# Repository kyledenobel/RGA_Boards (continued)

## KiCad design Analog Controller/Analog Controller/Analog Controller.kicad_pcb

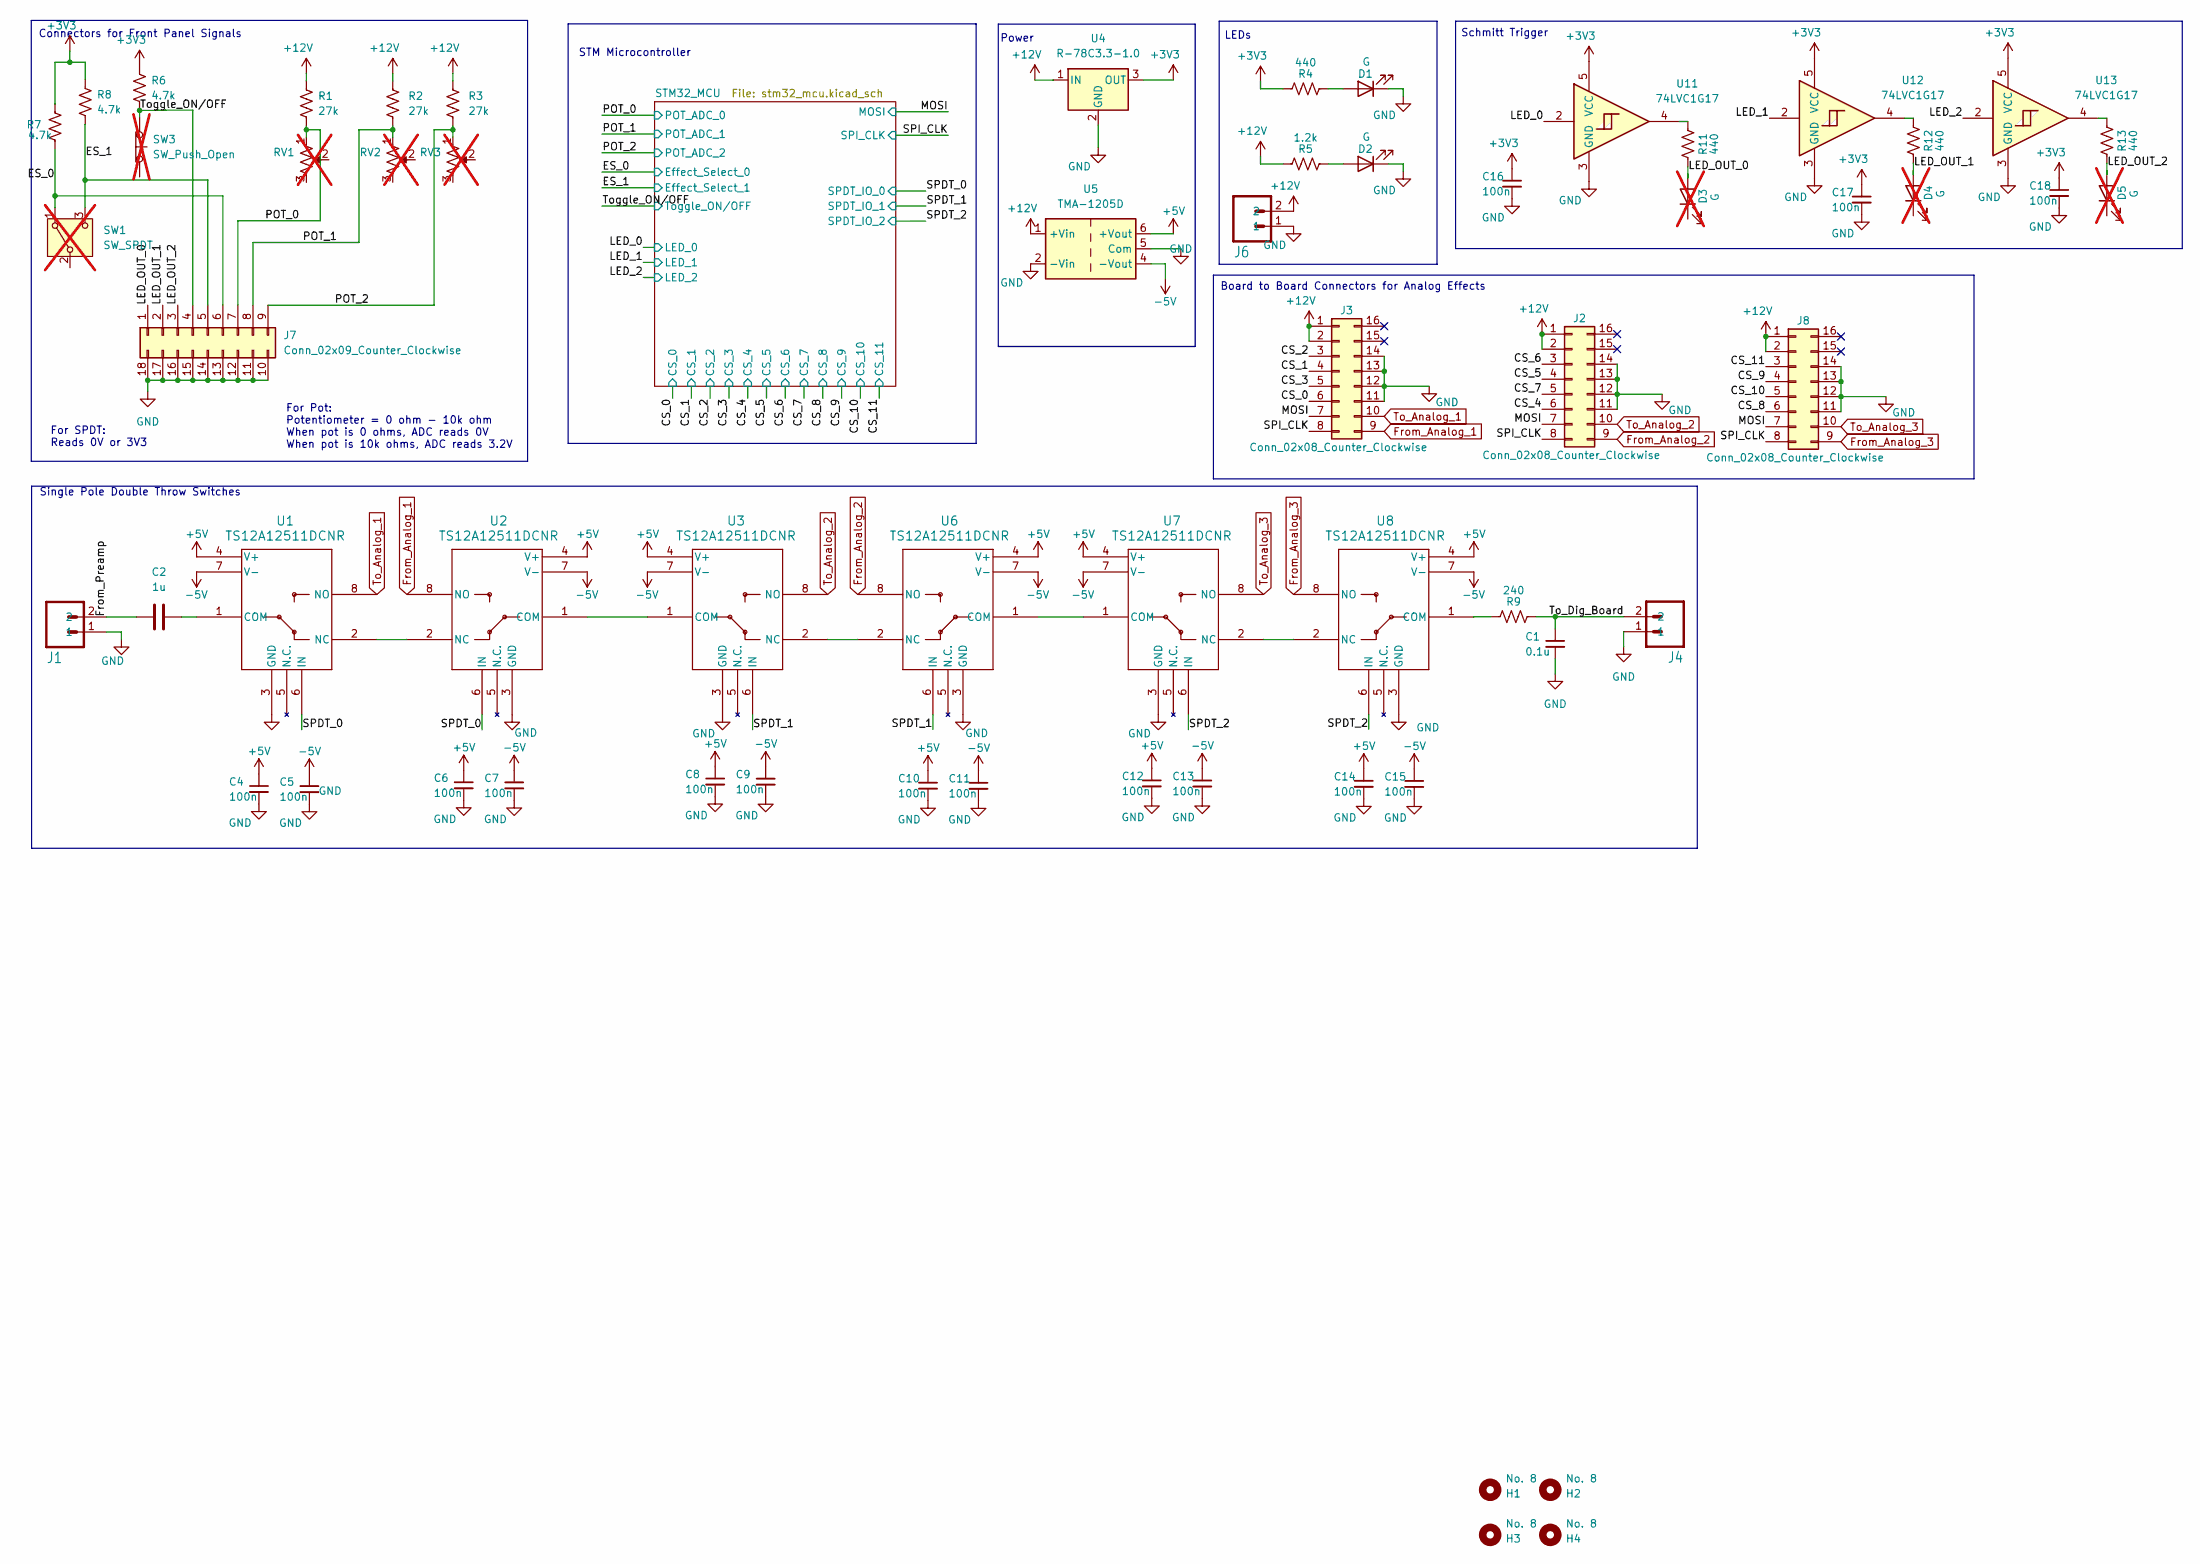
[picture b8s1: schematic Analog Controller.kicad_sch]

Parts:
C1: 0.1u; R_0603_1608Metric_Pad0.98x0.95mm_HandSolder
C2: 1u; C_0603_1608Metric
C4, C5, C6, C7, C8, C9, C10, C11, C12, C13, C14, C15, C16, C17, C18: 100n; R_0603_1608Metric_Pad0.98x0.95mm_HandSolder
D1, D2: G; LED_0603_1608Metric_Pad1.05x0.95mm_HandSolder
D3, D4, D5: G; LED_0603_1608Metric_Pad1.05x0.95mm_HandSolder; not fitted
H1, H2, H3, H4: No. 8; MountingHole_3.2mm_M3
J1, J4: MINIFIT-2-VERT; Molex_Mini-Fit_Jr_5566-02A_2x01_P4.20mm_Vertical
J2, J3, J8: Conn_02x08_Counter_Clockwise; PinSocket_2x08_P2.54mm_Vertical
J6: MINIFIT-2-VERT; Molex_Mega-Fit_76829-0102_2x01_P5.70mm_Vertical
J7: Conn_02x09_Counter_Clockwise; Molex_Micro-Fit_3.0_43045-1812_2x09_P3.00mm_Vertical
R1, R2, R3: 27k; R_0603_1608Metric_Pad0.98x0.95mm_HandSolder
R4, R11, R12, R13: 440; R_0603_1608Metric_Pad0.98x0.95mm_HandSolder
R5: 1.2k; R_0603_1608Metric_Pad0.98x0.95mm_HandSolder
R6, R7, R8: 4.7k; R_0603_1608Metric_Pad0.98x0.95mm_HandSolder
R9: 240; R_0603_1608Metric_Pad0.98x0.95mm_HandSolder
RV1, RV2, RV3: R_Potentiometer_US; not fitted
SW1: SW_SPDT; not fitted
SW3: SW_Push_Open; not fitted
U1, U2, U3, U6, U7, U8: TS12A12511DCNR; DCN8
U4: R-78C3.3-1.0; Converter_DCDC_RECOM_R-78E-0.5_THT
U5: TMA-1205D; Converter_DCDC_TRACO_TMA-05xxD_12xxD_Dual_THT
U11, U12, U13: 74LVC1G17; SOT-23-5

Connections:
+3V3: C16.1, C17.1, C18.1, R4.2, R6.1, R7.1, R8.1, U4.3 (OUT), U11.5 (VCC), U12.5 (VCC), U13.5 (VCC); also elsewhere on the board
+5V: C4.1, C6.1, C8.1, C10.1, C12.1, C14.1, U1.4 (V+), U2.4 (V+), U3.4 (V+), U5.6 (+Vout), U6.4 (V+), U7.4 (V+), U8.4 (V+)
+12V: J2.1, J2.2, J3.1, J3.2, J6.2, J8.1, J8.2, R1.1, R2.1, R3.1, R5.2, U4.1 (IN), U5.1 (+Vin)
-5V: C5.1, C7.1, C9.1, C11.1, C13.1, C15.1, U1.7 (V-), U2.7 (V-), U3.7 (V-), U5.4 (-Vout), U6.7 (V-), U7.7 (V-), U8.7 (V-)
/CS_0: J3.6; also elsewhere on the board
/CS_1: J3.4; also elsewhere on the board
/CS_2: J3.3; also elsewhere on the board
/CS_3: J3.5; also elsewhere on the board
/CS_4: J2.6; also elsewhere on the board
/CS_5: J2.4; also elsewhere on the board
/CS_6: J2.3; also elsewhere on the board
/CS_7: J2.5; also elsewhere on the board
/CS_8: J8.6; also elsewhere on the board
/CS_9: J8.4; also elsewhere on the board
/CS_10: J8.5; also elsewhere on the board
/CS_11: J8.3; also elsewhere on the board
/ES_0: J7.6, R7.2, SW1.1 (A); also elsewhere on the board
/ES_1: J7.5, R8.2, SW1.3 (C); also elsewhere on the board
/From_Preamp: C2.1, J1.2
/LED_0: U11.2; also elsewhere on the board
/LED_1: U12.2; also elsewhere on the board
/LED_2: U13.2; also elsewhere on the board
/LED_OUT_0: D3.2 (A), J7.1, R11.1
/LED_OUT_1: D4.2 (A), J7.2, R12.1
/LED_OUT_2: D5.2 (A), J7.3, R13.1
/MOSI: J2.7, J3.7, J8.7; also elsewhere on the board
/POT_0: J7.7, R1.2, RV1.1; also elsewhere on the board
/POT_1: J7.8, R2.2, RV2.1; also elsewhere on the board
/POT_2: J7.9, R3.2, RV3.1; also elsewhere on the board
/SPDT_0: U1.6 (IN), U2.6 (IN); also elsewhere on the board
/SPDT_1: U3.6 (IN), U6.6 (IN); also elsewhere on the board
/SPDT_2: U7.6 (IN), U8.6 (IN); also elsewhere on the board
/SPI_CLK: J2.8, J3.8, J8.8; also elsewhere on the board
/To_Dig_Board: C1.1, J4.2, R9.1
/Toggle_ON/OFF: J7.4, R6.2, SW3.1 (A); also elsewhere on the board
From_Analog_1: J3.9, U2.8 (NO)
From_Analog_2: J2.9, U6.8 (NO)
From_Analog_3: J8.9, U8.8 (NO)
GND: C1.2, C4.2, C5.2, C6.2, C7.2, C8.2, C9.2, C10.2, C11.2, C12.2, C13.2, C14.2, C15.2, C16.2, C17.2, C18.2, D1.1 (K), D2.1 (K), J1.1, J2.11, J2.12, J2.13, J2.14, J3.11, J3.12, J3.13, J3.14, J4.1, J6.1, J7.10, J7.11, J7.12, J7.13, J7.14, J7.15, J7.16, J7.17, J7.18, J8.11, J8.12, J8.13, J8.14, U1.3 (GND), U2.3 (GND), U3.3 (GND), U4.2 (GND), U5.2 (-Vin), U5.5 (Com), U6.3 (GND), U7.3 (GND), U8.3 (GND), U11.3 (GND), U12.3 (GND), U13.3 (GND); also elsewhere on the board
unnamed: D1.2 (A), R4.1
unnamed: D2.2 (A), R5.1
unnamed: R11.2, U11.4
unnamed: R12.2, U12.4
unnamed: R13.2, U13.4
unnamed: C2.2, U1.1 (COM)
unnamed: U1.2 (NC), U2.2 (NC)
unnamed: U2.1 (COM), U3.1 (COM)
unnamed: U3.2 (NC), U6.2 (NC)
unnamed: U6.1 (COM), U7.1 (COM)
unnamed: U7.2 (NC), U8.2 (NC)
unnamed: R9.2, U8.1 (COM)
To_Analog_1: J3.10, U1.8 (NO)
To_Analog_2: J2.10, U3.8 (NO)
To_Analog_3: J8.10, U7.8 (NO)

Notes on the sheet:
LEDs
For SPDT: Reads 0V or 3V3
Connectors for Front Panel Signals
Schmitt Trigger
STM Microcontroller
For Pot: Potentiometer = 0 ohm - 10k ohm When pot is 0 ohms, ADC reads 0V When pot is 10k ohms, ADC reads 3.2V
Board to Board Connectors for Analog Effects
Power
Single Pole Double Throw Switches

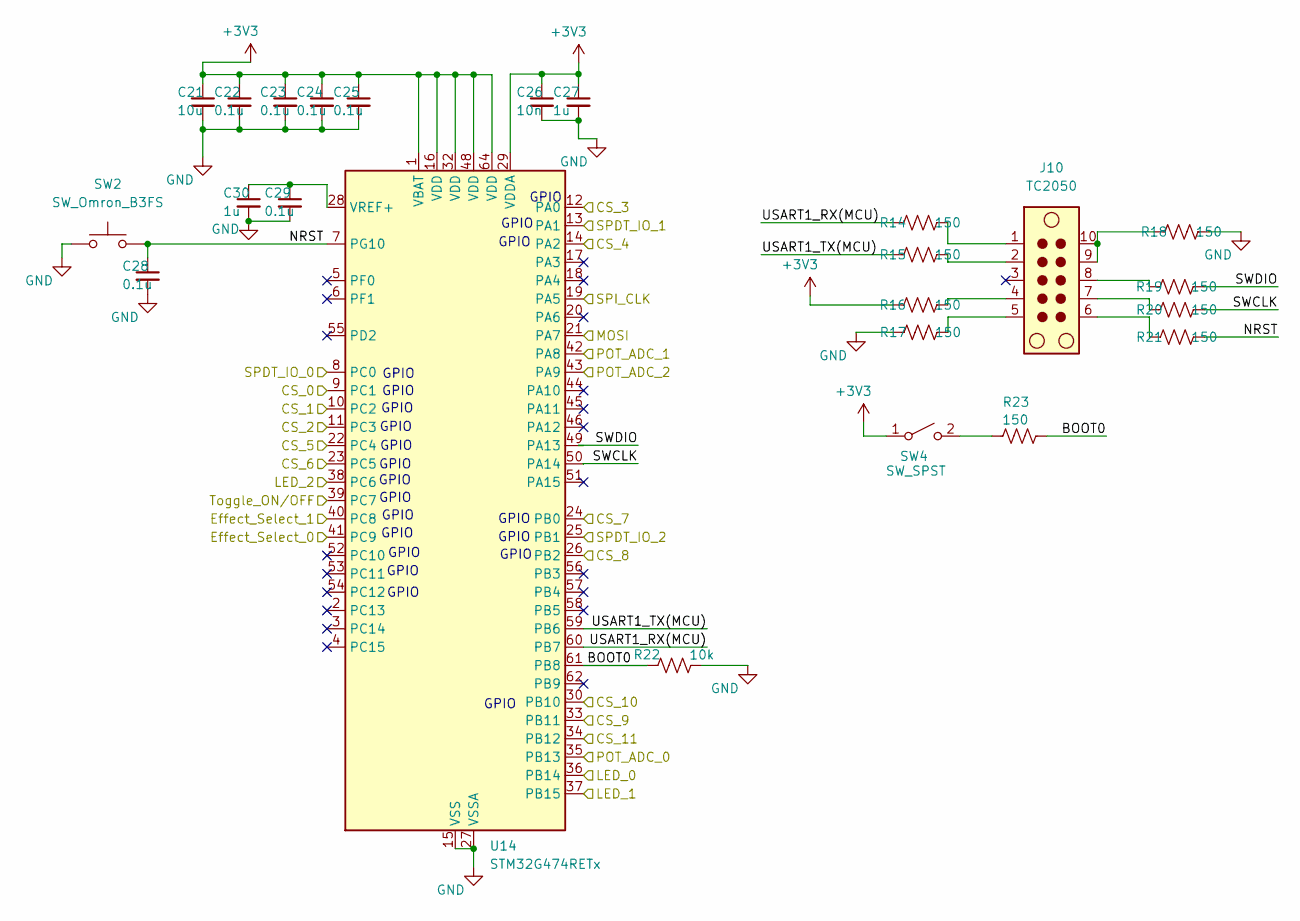
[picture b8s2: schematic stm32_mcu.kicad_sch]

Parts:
C21: 10u; R_0603_1608Metric_Pad0.98x0.95mm_HandSolder
C22, C23, C24, C25, C28, C29: 0.1u; R_0603_1608Metric_Pad0.98x0.95mm_HandSolder
C26: 10n; R_0603_1608Metric_Pad0.98x0.95mm_HandSolder
C27, C30: 1u; R_0603_1608Metric_Pad0.98x0.95mm_HandSolder
J10: TC2050; Tag-Connect_TC2050-IDC-FP_2x05_P1.27mm_Vertical
R14, R15, R16, R17, R18, R19, R20, R21, R23: 150; R_0603_1608Metric_Pad0.98x0.95mm_HandSolder
R22: 10k; R_0603_1608Metric_Pad0.98x0.95mm_HandSolder
SW2: SW_Omron_B3FS; SW_SPST_Omron_B3FS-101xP
SW4: SW_SPST; SW_SPST_B3U-1000P
U14: STM32G474RETx; LQFP-64_10x10mm_P0.5mm

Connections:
+3V3: C21.1, C22.1, C23.1, C24.1, C25.1, C26.1, C27.1, R16.1, SW4.1 (A), U14.1 (VBAT), U14.16 (VDD), U14.29 (VDDA), U14.32 (VDD), U14.48 (VDD), U14.64 (VDD); also elsewhere on the board
/CS_0: U14.9 (PC1); also elsewhere on the board
/CS_1: U14.10 (PC2); also elsewhere on the board
/CS_2: U14.11 (PC3); also elsewhere on the board
/CS_3: U14.12 (PA0); also elsewhere on the board
/CS_4: U14.14 (PA2); also elsewhere on the board
/CS_5: U14.22 (PC4); also elsewhere on the board
/CS_6: U14.23 (PC5); also elsewhere on the board
/CS_7: U14.24 (PB0); also elsewhere on the board
/CS_8: U14.26 (PB2); also elsewhere on the board
/CS_9: U14.33 (PB11); also elsewhere on the board
/CS_10: U14.30 (PB10); also elsewhere on the board
/CS_11: U14.34 (PB12); also elsewhere on the board
/ES_0: U14.41 (PC9); also elsewhere on the board
/ES_1: U14.40 (PC8); also elsewhere on the board
/LED_0: U14.36 (PB14); also elsewhere on the board
/LED_1: U14.37 (PB15); also elsewhere on the board
/LED_2: U14.38 (PC6); also elsewhere on the board
/MOSI: U14.21 (PA7); also elsewhere on the board
/POT_0: U14.35 (PB13); also elsewhere on the board
/POT_1: U14.42 (PA8); also elsewhere on the board
/POT_2: U14.43 (PA9); also elsewhere on the board
/SPDT_0: U14.8 (PC0); also elsewhere on the board
/SPDT_1: U14.13 (PA1); also elsewhere on the board
/SPDT_2: U14.25 (PB1); also elsewhere on the board
/SPI_CLK: U14.19 (PA5); also elsewhere on the board
/STM32_MCU/BOOT0: R22.2, R23.2, U14.61 (PB8)
/STM32_MCU/NRST: C28.1, R21.2, SW2.2, U14.7 (PG10)
/STM32_MCU/SWCLK: R20.2, U14.50 (PA14)
/STM32_MCU/SWDIO: R19.2, U14.49 (PA13)
/STM32_MCU/USART1_RX(MCU): R14.1, U14.60 (PB7)
/STM32_MCU/USART1_TX(MCU): R15.1, U14.59 (PB6)
/Toggle_ON/OFF: U14.39 (PC7); also elsewhere on the board
GND: C21.2, C22.2, C23.2, C24.2, C25.2, C26.2, C27.2, C28.2, C29.2, C30.2, R17.1, R18.2, R22.1, SW2.1, U14.15 (VSS), U14.27 (VSSA), U14.31 (VSS), U14.47 (VSS), U14.63 (VSS); also elsewhere on the board
unnamed: J10.1, R14.2
unnamed: J10.2, R15.2
unnamed: J10.4, R16.2
unnamed: J10.5, R17.2
unnamed: J10.6, R21.1
unnamed: J10.7, R20.1
unnamed: J10.8, R19.1
unnamed: J10.9, J10.10, R18.1
unnamed: R23.1, SW4.2 (B)
unnamed: C29.1, C30.1, U14.28 (VREF+)

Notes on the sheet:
GPIO

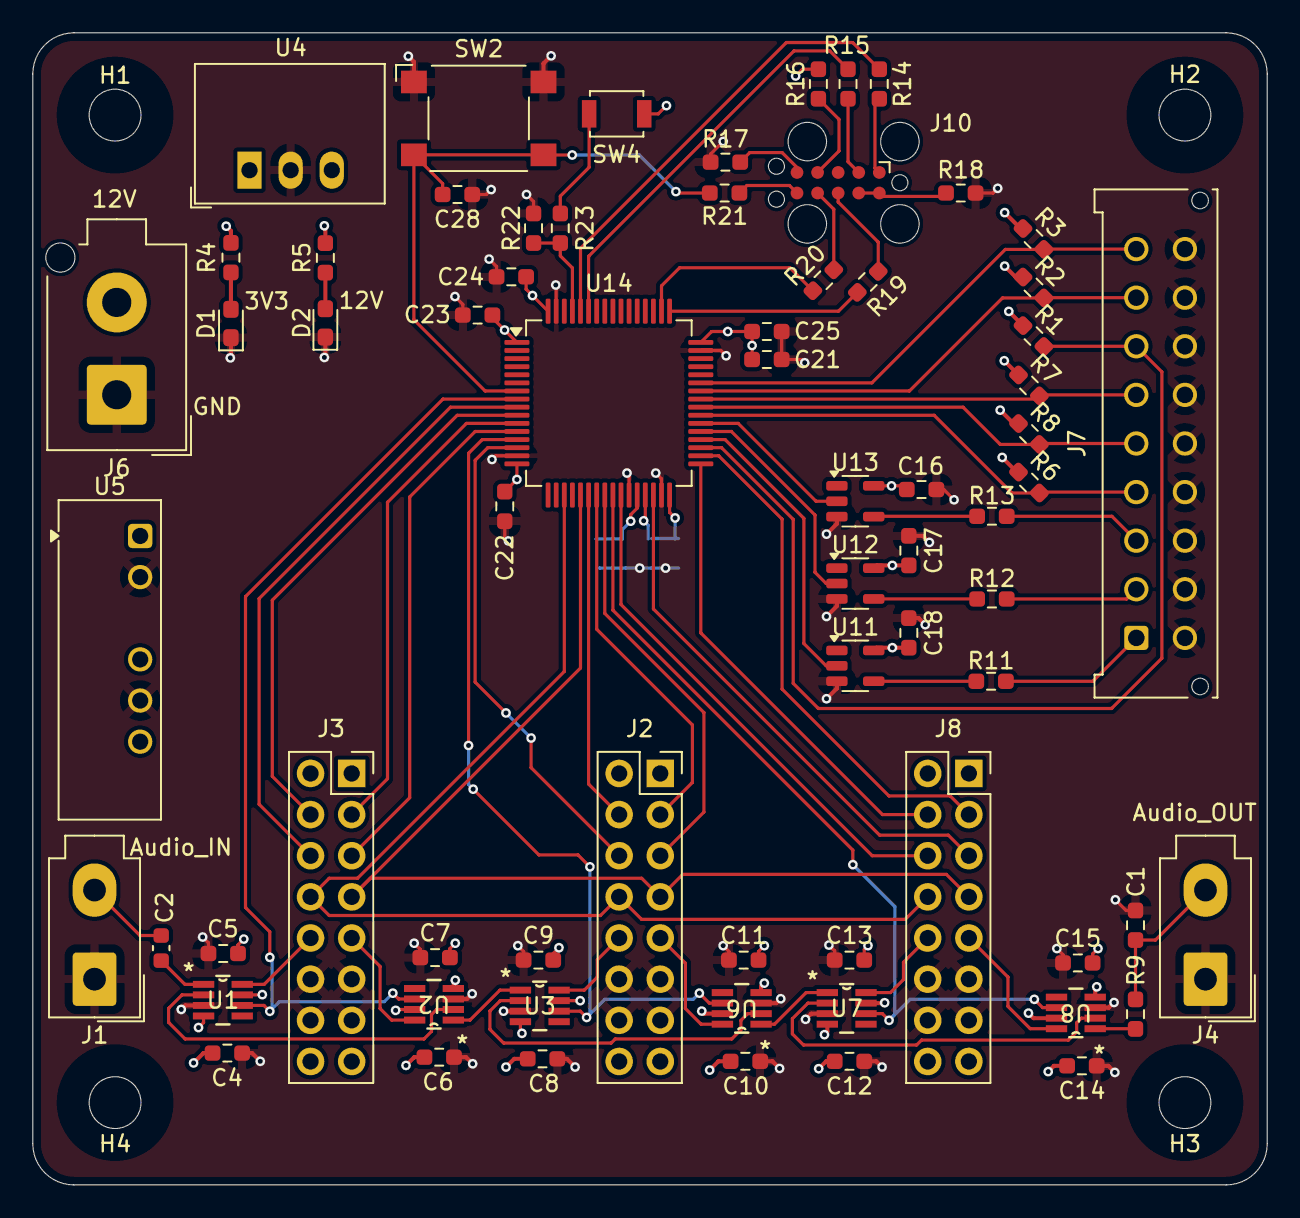
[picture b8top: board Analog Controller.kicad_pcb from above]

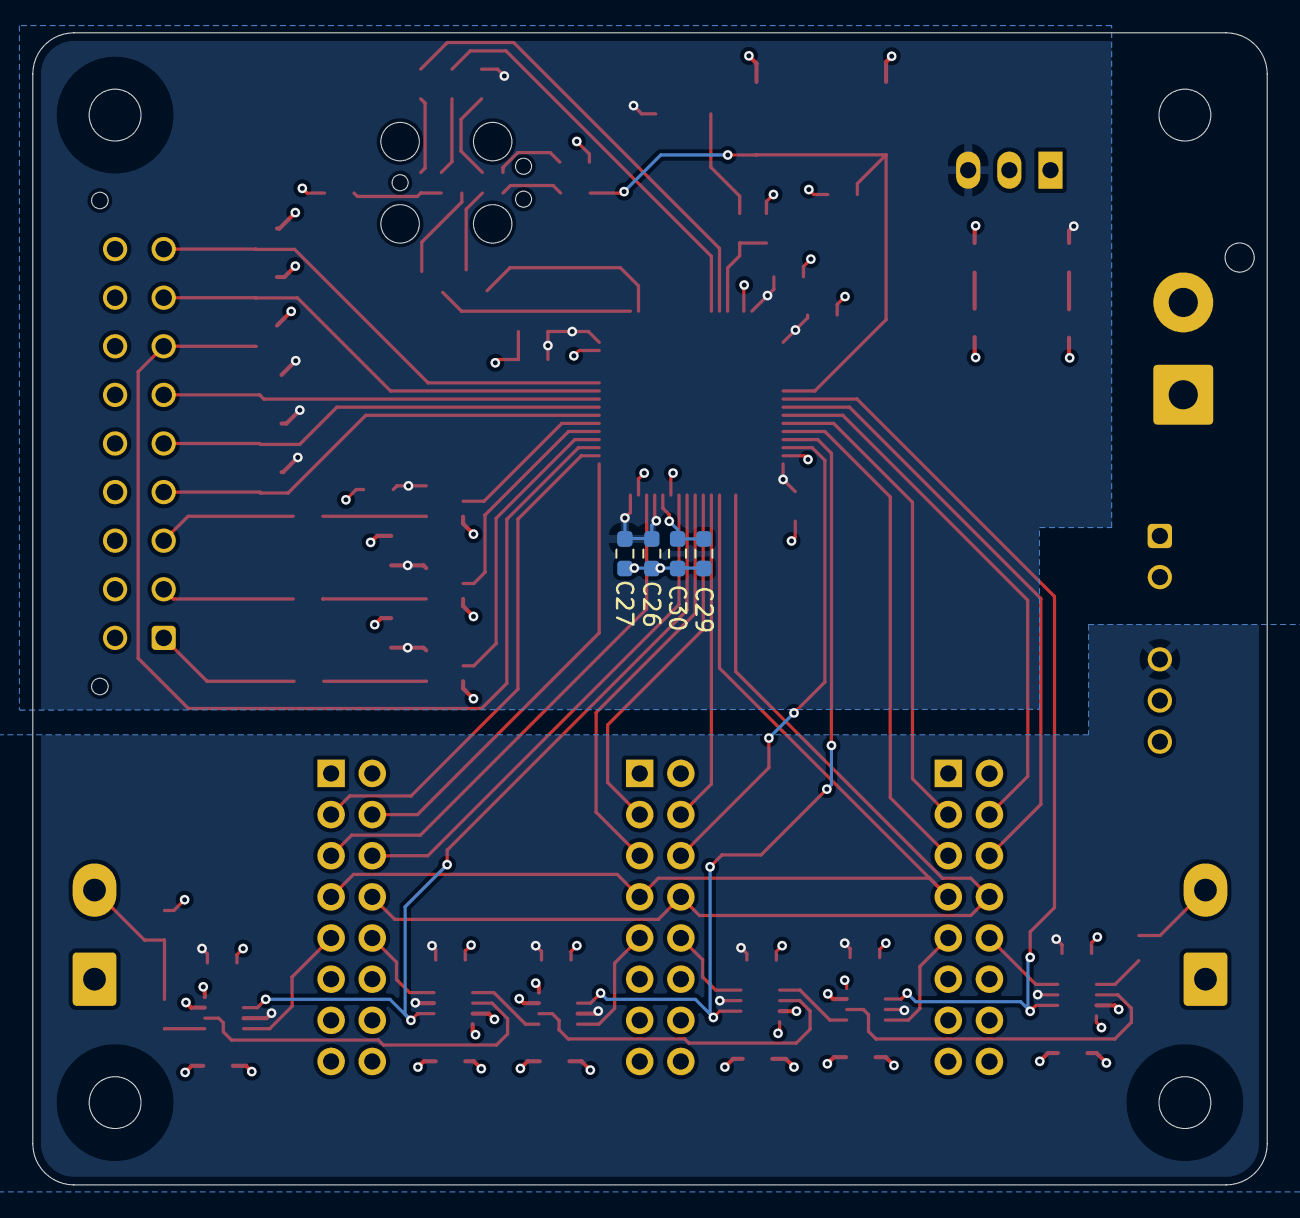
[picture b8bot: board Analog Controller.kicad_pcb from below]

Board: 4 copper layers, 76.2 x 71.1 mm, 77 parts (4 on the bottom side), 70 nets.

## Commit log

2026-01-23 bigmuffripoff
    cool
2026-01-23 fixed 5 silkscreens
    boo
2026-01-25 Update README.md to include instructions on how to use git issues to keep organized
2026-02-01 datasheet updates
    womp womp
2026-02-01 starting to redo board layout
    also finished changing the schematic
2026-02-10 did half of the changes
    gonna finish the next have next time
2026-02-10 getting closer on finishing layout
2026-02-11 updateded datasheet
    upda
2026-02-14 Initial Commit
    Added Power Board and Analog Controller
2026-02-15 Finished schematic and layout of power board
2026-02-15 please dont break plsplspls
2026-02-16 no sure
2026-02-22 made digital and recording board schematic
2026-02-22 updated schematic to use +/-5 DCDC
2026-02-22 added datasheet to new DCDC converter
2026-02-22 look mom i did it
    the board is done
2026-02-22 modified power for proper amp rating of daisy seed
2026-02-22 added datasheets to new dcdc converters
2026-02-23 layout for digital board is essentially complete
    current draw for the screen may fuck us if it is too high
2026-02-23 Completed Analog Controller Board
    Completed Analog Controller Board schematic and pcb layout :)
2026-02-23 im pushing in case kicad crashes again
    also the board was significantly updated
2026-02-23 moved some silks
2026-02-23 moved another
2026-02-24 added fun silk screens
2026-02-24 updated schematic of digital and recording board to use 2 pin molex for power and guitar signals
2026-02-24 corrected connectors
2026-02-24 whoops forgot this one
2026-02-25 Reduced minimum clearance on digicorder
2026-02-26 changes for digital and recording board. pass to marco
2026-03-04 created kiCad project for overdrive
2026-03-06 finished Overdrive schematic
2026-03-06 updated datasheet to point to digikey for 1k pot
2026-03-08 Mostly Finished Power Amp Board
2026-03-08 added important datasheets
2026-03-09 finished schematic for phase 90 and implemented the correct op-amps for overdrive
2026-03-09 changed out potentiometer for one that can do higher analog voltages
2026-03-09 new big muff made
2026-03-09 new big muff completed
2026-03-09 removed the old diodes from before
2026-03-09 scooted my silks
2026-03-09 updated phase 90 to not need 12 to 3 converted
2026-03-09 finished overdrive layout
2026-03-09 finished board except for silk screen
2026-03-10 silks have been scooted
2026-03-10 Added new stm32 microcontroller, redid pcb layout
2026-03-10 removed all .DS_Store files and updated .gitignore to no longer have them included in the repo. Also started board reviews
2026-03-10 finished board reviews - Kyle
2026-03-10 Completed Power Board
2026-03-11 connector for big muff updated
2026-03-11 updated design rules for OshPark
2026-03-11 big muff connector fixed i think?
2026-03-11 fixed connector also?
2026-03-11 power amp design rule changes
2026-03-11 overdrive updates to conform with new connector
2026-03-11 Completed Pre Amp
2026-03-12 Added top copper gnd layer on pre amp
2026-03-12 added buffer to schematic of power amp
2026-03-12 Incorporated changes from demo
2026-03-12 added buffers and caps for op-amps on effect boards
2026-03-12 just absolutely lapped kyle
    get fucked kyle
2026-03-12 added buffer to big muff
2026-03-12 addressed Marco's design review
2026-03-12 fixes for Marco's dr
2026-03-12 more clearances for power board screw terminals
2026-03-12 more clearances for pre-amp screw terminals
2026-03-12 i fixed kyles fuckery
    hes the goat tho
2026-03-12 more clearance not thermal reliefs
2026-03-12 generated gerbs
2026-03-12 Power strip board part 1
2026-03-12 zips
2026-03-12 Power strip board part 2
2026-03-13 zip files
2026-03-15 Power amp review
2026-03-15 new review for power amp
2026-03-15 overdrive design review
2026-03-15 big muff board review
2026-03-16 board fixes for Overdrive based off of Joseph's reviews
2026-03-16 made changes for power
2026-03-16 fixed board again
2026-03-18 fixed usb pitch issue
2026-03-18 fixed it
2026-03-19 Analog controller and power board BOMs
2026-03-19 pre amp stage bom
2026-03-20 gerbs
2026-03-20 created master BOM for all boards
2026-03-25 boms suck man
    added csvs of the digikey cart as well as highlighted the excel
2026-03-26 everything green has been paid for
2026-03-26 updated BOM and finished orders
